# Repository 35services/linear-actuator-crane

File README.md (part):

# RC Crane – Stepper Linear Actuator Controller

**All CAD renderings and printable STLs:** [`cad/`](cad/README.md). **Carrier PCB, ready to order:**
[`pcb/`](pcb/README.md), as a through‑hole version for hand soldering or an SMD version
assembled by JLCPCB. **Advanced board** with an ESP32‑S3, 4 stepper drivers, 16 servo/ESC
outputs, RC and CRSF/SBUS inputs: [`pcb/advanced/`](pcb/advanced/README.md), or the same as a
[stack of two smaller boards](pcb/advanced-stack/README.md). The concept sketch
that started it is [`gemini.jpeg`](gemini.jpeg).

Drive two mini stepper‑motor linear actuators (2‑phase, 4‑wire, lead screw + slider) from
normal RC receiver channels to work a crane on an RC model vehicle:

* **Boom lift:** actuator 1 raises and lowers the boom.
* **Telescope:** actuator 2, lying on top of the boom, extends the inner boom section.

Features:

* **No end switches.** On power‑up both actuators home themselves using **sensorless
  homing** (TMC2209 StallGuard). If stall detection isn't reliable on your motors, they fall
  back to **hard‑stop homing**: each one drives into its mechanical end at low current.
* **Plug‑and‑play with RC.** The ESP32 reads a standard servo PWM signal (1000–2000 µs) from
  one receiver channel per actuator.
* **Battery friendly.** Lead screws are self‑locking, so the drivers are switched off when
  idle and the load still holds.

### Overview

| Crane, boom down | Crane, boom up 55°, telescope out |
|---|---|
|  |  |

**Bowden drives** ([use cases](cad/use-cases/README.md)): the actuator sits flat on the vehicle
and pushes or pulls a filament in a PTFE tube.

| Outriggers under the chassis | Crane with both actuators on the deck |
|---|---|
|  |  |

**Actuators** ([CAD](cad/README.md), [comparison](docs/actuator_comparison.md)):

| Stepper slider in a printed housing (used now) | 28BYJ‑48 + T8 lead screw (cheap stepper) | N20 + M4 lead screw (DC) |
|---|---|---|
|  |  |  |
| 75 mm stroke, 15–20 mm/s, exact position | 75 mm stroke, ≈ 2.7 mm/s, exact position, hall home sensor | 80 mm stroke, current‑sense homing |

**Boards** ([PCB overview](pcb/README.md)):

| Carrier, THT | Carrier, SMD (JLCPCB) | Advanced, ESP32‑S3 |
|---|---|---|
|  |  |  |
| ESP32‑C3, 2 × TMC2209, 80 × 64 mm | the same, SMD parts assembled | 4 × TMC2209, 16 PWM outputs, 100 × 100 mm |

| Advanced stack: top board | Advanced stack: bottom board | Web settings page |
|---|---|---|
|  |  |  |
| DevKitC‑1 + 4 drivers, 84 × 76 mm | PCA9685, inputs, power | [try it in the browser](https://raw.githack.com/35services/linear-actuator-crane/main/firmware/web_preview/index.html) |

---

## 1. How it works

```
                          ┌──── servo PWM (CH a) ──┐
 Transmitter ──radio──► RC receiver                ▼
                          └──── servo PWM (CH b) ──► ESP32-C3
                                                     │   ▲
                       shared UART + EN, own STEP/DIR│   │ DIAG (OR'ed)
                                     ┌───────────────┴───┴──────────────┐
                                     ▼                                  ▼
                              TMC2209 #0 (addr 0)               TMC2209 #1 (addr 1)
                                     │                                  │
                              actuator 1: boom lift             actuator 2: telescope
```

1. **Power‑up:** the ESP32 configures both TMC2209s over one shared UART line. They have
   different addresses, set with the MS1/MS2 pins.
2. **Homing,** one actuator at a time. The **telescope goes first**, so the boom moves with
   the shortest lever.
   * The actuator drives toward its retracted end at low current.
   * With **StallGuard**, the homing driver sees the motor load spike and pulls `DIAG`
     high, so the ESP32 stops right away. Only the homing driver has its stall output
     enabled, so the two `DIAG` lines can share one GPIO.
   * Without StallGuard (or if no stall is detected), the motor runs for the full stroke
     plus a small margin. At low current it just skips a few steps against the end, which
     does no harm, and that point becomes position 0.
   * Optionally, homing is skipped after a clean stop, see
     [Skipping homing after a clean stop](#skipping-homing-after-a-clean-stop).
3. **Run:** each RC channel controls one actuator, in either
   * **Position mode:** stick or knob position = actuator position. The default for the
     boom lift, best on a knob or slider.
   * **Rate mode:** stick deflection = speed. The default for the telescope, best on a
     self‑centring stick.
   Soft limits keep each slider a little away from both ends, so it never crashes again
   after homing.
4. **Failsafe:** if no valid RC pulse arrives on a channel for 250 ms, that actuator stops.

---

## 2. Components

| # | Qty | Part | Notes | ~Price |
|---|-----|------|-------|--------|
| 1 | **2** | Mini stepper linear actuator (the AliExpress part) | 2‑phase, 4‑wire. 18° (20 steps/rev), M3 screw with **0.5 mm lead**, **~75 mm stroke** (counted from the listing photo, see [Speed](#speed-how-fast-can-it-move)) | 2 × €11 |
| 2 | 1 | **ESP32‑C3 SuperMini** (or Seeed XIAO ESP32‑C3) | Tiny, 3.3 V logic, USB‑C | €3 |
| 3 | **2** | **TMC2209 stepper driver module** (BigTreeTech v1.3, FYSETC or similar, *UART version*) | Quiet (StealthChop), current set over UART, **StallGuard for sensorless homing**, 4.75–29 V | 2 × €4 |
| 4 | **2** | Electrolytic capacitor **100 µF, ≥ 25 V** (35 V recommended) | One across each driver's VM/GND, close to the module. **Required.** | €0.40 |
| 5 | 1 | Resistor **1 kΩ** | Single‑wire UART (between TX and the shared PDN_UART line) | – |
| 6 | 2 | Diode **1N4148** (or any small signal diode) | OR both `DIAG` outputs onto one GPIO | – |
| 7 | 1 | Resistor **10 kΩ** | Pull‑down on the shared `DIAG` line | – |
| 8 | 2 + 2 | Resistor **1 kΩ** + Schottky diode **BAT85** per RC channel | Series resistor + clamp to 3V3, so any receiver signal level (3.3 V, 5 V or the 7.4 V BEC rail) is safe | – |
| 9 | 1 | **LM2940CT‑5.0** low‑dropout regulator (TO‑220) | 5 V for the ESP32 from the 6 V / 7.4 V BEC rail. See [Power](#4-power) | €1.50 |
| 10 | 1 + 1 | Capacitors **470 nF** ceramic (LDO input) + **47 µF / 16 V** electrolytic (LDO output) | The LM2940 needs ≥ 22 µF on its output to be stable | – |
| 11 | 1 | Schottky diode **1N5817** | LDO → ESP32 5V pin. Stops USB from back‑feeding the regulator while flashing | – |
| 13 | 2 | Servo extension lead | Receiver channels → board | €2 |
| 15 | 1 set | Nesting square tubes (aluminium/brass, e.g. 16×12 and 11×7 mm) | Telescopic boom. See [Mechanics](#5-mechanics) | €5 |
| 16 | | [Carrier PCB](pcb/README.md) (or perfboard), JST‑XH connectors, female pin headers, heat‑shrink | | |

**Vehicle drive (for reference):** Hobbywing **QuicRun Fusion SE** 1800 kV crawler motor/ESC
combo. It takes 2–3S LiPo (up to 12.6 V) and has a switch‑mode **BEC of 6 V or 7.4 V
(switchable), 4 A**. The crane electronics are designed for both BEC settings.

### Why the TMC2209?

| Driver | Sensorless homing | Noise | Current setting | Verdict |
|--------|-------------------|-------|-----------------|---------|
| **TMC2209** | ✅ StallGuard4 | silent | software (UART) | **Recommended** |
| TMC2208 | ❌ | silent | potentiometer/UART | OK, hard‑stop homing only |
| A4988 / DRV8825 | ❌ | loud | potentiometer | Works, but crude for tiny motors |
| DRV8833 (H‑bridge) | ❌ | – | none (voltage‑driven) | Only for 5 V motors on a 5 V supply. No current limit |

> **What's the little potentiometer on the TMC2209 module for?** The onboard pot sets
> motor current in standalone mode via VREF, but since our firmware controls current over
> UART and disables VREF with `I_scale_analog(false)`, the pot has no effect and can be
> ignored.

---

## 3. Wiring diagram

Both drivers are wired the same way. The only differences are **STEP/DIR**, the **address
pins** and the **diode on DIAG**.

```
  2S/3S LiPo ──► Hobbywing QuicRun Fusion SE (ESC) ── BEC 6 V / 7.4 V, 4 A ──► RC receiver
                                                                                  │
         BEC + / − arrive on the board through the RC servo leads (CH a, CH b) ◄──┘
                     │
       ┌─────────────┤
       │ BEC + (VM)  │ GND (−)
       │      ┌──────┘
       │ (+)  │ (-)
       ├──────┼────────────────────────────────────────┐
       │      │      100 µF                    │      │      100 µF
       ▼      ▼     ┌─┤├─┐                     ▼      ▼     ┌─┤├─┐
   ┌───────────────────────────┐           ┌───────────────────────────┐
   │   TMC2209 #0 (boom lift)  │           │   TMC2209 #1 (telescope)  │
   │                           │           │                           │
   │  VM / GND ◄── BEC         │           │  VM / GND ◄── BEC         │
   │  1A 1B 2A 2B ──► actuator 1           │  1A 1B 2A 2B ──► actuator 2
   │                           │           │                           │
   │  VIO ◄── 3V3              │           │  VIO ◄── 3V3              │
   │  GND ◄── GND              │           │  GND ◄── GND              │
   │  MS1 ◄── GND  ┐ addr 0    │           │  MS1 ◄── 3V3  ┐ addr 1    │
   │  MS2 ◄── GND  ┘           │           │  MS2 ◄── GND  ┘           │
   │                           │           │                           │
   │  STEP ◄── GPIO4           │           │  STEP ◄── GPIO0           │
   │  DIR  ◄── GPIO5           │           │  DIR  ◄── GPIO1           │
   │  EN   ◄── GPIO6 (shared)  │           │  EN   ◄── GPIO6 (shared)  │
   │  DIAG ──►|──┐  1N4148     │           │  DIAG ──►|──┐  1N4148     │
   │             │             │           │             │             │
   │  PDN_UART ◄─┼──────┬──────────────────────── PDN_UART              │
   └─────────────┼──────┼──────┘           └─────────────┼─────────────┘
                 │      │                                │
                 │      │       DIAG (shared) ◄──────────┘
                 ├──────┼──────────────────────► GPIO7 ──[10 kΩ]── GND
                        │
                        ├──────────────────────► GPIO20 (RX)
                        └──[1 kΩ]──────────────► GPIO21 (TX)

                         470 nF        47 µF
                           ┴             ┴
   BEC + (6/7.4 V) ──► IN ┤ LM2940-5.0 ├ OUT ──►|── 1N5817 ──► SuperMini 5V
                              │ GND
                              ┴

   ┌────────────────────────┐                     ┌───────────────────────┐
   │     ESP32-C3 SuperMini │                     │      RC receiver      │
   │                        │                     │                       │
   │  5V  ◄── LM2940 (above)│          BEC + ◄──── + (6 V / 7.4 V)      │
   │  GND ◄──────────────────────────────────────── −                     │
   │  GPIO3  ◄──┬──[1 kΩ]──────────────────────────── S  CH a: boom lift   │
   │            └──►|── 3V3  (BAT85 clamp)         │                       │
   │  GPIO10 ◄──┬──[1 kΩ]──────────────────────────── S  CH b: telescope   │
   │            └──►|── 3V3  (BAT85 clamp)         └───────────────────────┘
   └────────────────────────┘
```

Each actuator connects to its driver exactly as before: one coil on `1A/1B`, the other on
`2A/2B`.

### Pin table

| ESP32‑C3 | → | Connects to | Purpose |
|----------|---|-------------|---------|
| GPIO4 | → | TMC2209 #0 STEP | boom lift step pulses |
| GPIO5 | → | TMC2209 #0 DIR | boom lift direction |
| GPIO0 | → | TMC2209 #1 STEP | telescope step pulses |
| GPIO1 | → | TMC2209 #1 DIR | telescope direction |
| GPIO6 | → | EN of **both** drivers | LOW = drivers on, HIGH = off |
| GPIO7 | ← | DIAG of **both**, through a diode each, plus 10 kΩ to GND | HIGH = stall detected |
| GPIO21 (TX) | → 1 kΩ → | PDN_UART of **both** | UART write |
| GPIO20 (RX) | ← | PDN_UART of **both** | UART read (direct) |
| GPIO3 | ← 1 kΩ ← | receiver CH a signal (BAT85 clamp to 3V3) | boom lift servo PWM in |
| GPIO10 | ← 1 kΩ ← | receiver CH b signal (BAT85 clamp to 3V3) | telescope servo PWM in |
| 3V3 | → | VIO of both, MS1 of #1 | logic supply / address |
| GND | – | GND of both drivers (logic side) | **common ground** |
| 5V | ← 1N5817 ← | LM2940‑5.0 output (input: BEC + from the receiver) | ESP32 supply |

### Wiring gotchas

* **Driver addresses:** #0 has MS1 = MS2 = GND (address 0). #1 has **MS1 = 3V3**,
  MS2 = GND (address 1). If both drivers have the same address, the UART check at boot
  fails for one of them.
* **DIAG – the stall signal for homing without end switches.** The TMC2209 pulls its DIAG
  pin high when the motor stalls (StallGuard).
  * **During homing:** the ESP32 watches GPIO7 and stops the actuator the moment it hits the
    end of travel.
  * **One GPIO for both drivers:** each DIAG goes through a diode (anode at DIAG, cathode
    (the band) toward GPIO7), and a 10 kΩ pull‑down holds the line low when neither driver
    signals a stall. The firmware only enables the stall output on the axis that is
    homing, so it always knows which one stalled.
  * **It needs a wire:** DIAG is **not** one of the 16 StepStick socket pins. On most
    modules it's a separate pin, and its position differs between brands. On the carrier
    PCB, run a short female‑to‑male Dupont jumper from the module's DIAG pin to the
    single socket next to the driver: **J12** for the lift, **J13** for the telescope.
  * **Without the wires:** set `USE_STALLGUARD false`, and homing drives into the end stop
    at low current instead.

* **Find the coil pairs** with a multimeter. The two wires that show resistance between them
  (typically 5–30 Ω) are one coil. If an actuator moves the wrong way, swap the two wires of
  **one** coil, or flip that axis's `invert` flag in the firmware.
* **Never plug or unplug a motor while its driver is powered.** That kills TMC drivers.
* Pin order differs between TMC2209 brands. Go by the labels, not by position.
  * BTT v1.3: `PDN_UART` is the pin marked **RX** (`TX` is the same net). `DIAG` is on the
    extra pin header at the top.
  * Some clones need a solder bridge to connect PDN to the header pin. Check the module's
    pinout.
* **All grounds are common:** ESC/BEC −, receiver −, ESP32 GND, both TMC2209 GNDs. With
  the carrier PCB this happens automatically through the servo leads.
* **Receiver signal level:** most receivers output 3.3 V signals, but some put out the
  servo rail voltage (up to 7.4 V with this BEC). The ESP32 isn't 5 V tolerant, so each
  channel has a 1 kΩ series resistor and a BAT85 Schottky diode from the GPIO to 3V3
  (cathode, the band, to 3V3). Anything above about 3.6 V is clamped, with at most about
  4 mA flowing into the 3V3 rail. This works with every receiver and needs no jumper.
* **Never connect the BEC + to the SuperMini's 5V pin directly.** At 6 V the onboard
  regulator is already at its limit, and 7.4 V destroys it. Always go through the LM2940.
* **Strapping pins:** GPIO2, 8 and 9 on the C3 are strapping pins and are avoided. GPIO0/1
  are normal GPIOs on the SuperMini.

---

## 4. Power

* **Everything runs from the ESC's BEC.** There's no separate battery input. The BEC
  arrives on the board through the `+`/`−` pins of the RC servo leads.
* **Motors (TMC2209 VM):** straight from the BEC rail (6 V or 7.4 V).
  * The TMC2209 works from 4.75 V, and the two small steppers draw only about 0.3–0.6 A
    together, against the 4 A BEC.
  * A "5 V" mini stepper is fine at 6–7.4 V. The TMC2209 limits the **current**, so the
    voltage only adds a little speed headroom.
  * Plug in **both** RC leads, so the current is shared between two servo cables.
  * A servo plug put on backwards is harmless: `+` is the middle pin, so only signal and
    GND swap. That's why there's no reverse‑polarity diode.
  * Set the current per axis in firmware (the `run` column in `AXES`). Rule of thumb:
    `I = rated voltage / coil resistance`. Example: 5 V / 15 Ω ≈ 330 mA → use about 300 mA.
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
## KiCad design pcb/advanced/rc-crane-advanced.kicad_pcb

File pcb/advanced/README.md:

# Advanced board – ESP32‑S3, 4 steppers, 16 PWM outputs

A 100 × 100 mm two‑layer board for the bigger concept: the ESP32 as receiver, as a
multiplexer between receiver and servos/ESC, or reading the drive channels in "crane mode".

| | |
|---|---|
| ESP32 | **ESP32‑S3‑DevKitC‑1** in two 1×22 sockets, USB over the left board edge |
| Steppers | **4 × TMC2209** StepStick sockets on one UART (addresses 0–3), DIAG per driver, 4 × JST‑XH motor connectors |
| Outputs | **16 servo/ESC outputs** from a PCA9685 (I²C), `S + −` block like a receiver, 220 Ω per channel |
| Inputs | **4 RC PWM inputs** (`S + −` block, 1 kΩ + clamp to 3V3) and a **CRSF/SBUS port** for a serial receiver |
| Extras | I²C header (second PCA9685, display, …) |
| Power | everything from the BEC rail; drivers' motor supply selectable: BEC or 2–3S battery |
| Assembly | 39 SMD parts by JLCPCB (12 part types, **1 extended**: the PCA9685), the rest hand‑soldered |
| DRC | 0 violations, 0 unconnected |

> **Smaller footprint?** The same circuit as a [stack of two 84 × 76 mm boards](../advanced-stack/README.md).

> **Status:** the board is designed and checked (DRC, netlist), but not built or tested yet.
> The current firmware is for the small ESP32‑C3 board; the firmware for this board
> (4 axes, PCA9685 outputs, CRSF/SBUS, crane mode) is the next step.

> **Which remote control?** RC/ELRS on the CRSF port, a PlayStation controller through a
> Bluepad32 bridge, or a WiFi app: see [remote control options](../../docs/remote_control_comparison.md).

| Top | Bottom |
|---|---|
|  |  |

| 3D, from below | Copper + silkscreen, front | Copper + silkscreen, back (mirrored) |
|---|---|---|
|  |  |  |

---

## ESP32 pin assignment

The DevKitC‑1 lies on its side: **USB connectors over the left board edge**, antenna to the
right over a copper‑free area. J10 is the board's J1 header (top row), J11 its J3 header.
Every socket pin is labelled on the silkscreen.

| GPIO | Function | | GPIO | Function |
|---|---|---|---|---|
| 4 / 5 | STEP / DIR driver #0 | | 1 | RC input 1 |
| 6 / 7 | STEP / DIR driver #1 | | 2 | RC input 2 |
| 15 / 16 | STEP / DIR driver #2 | | 42 | RC input 3 |
| 17 / 18 | STEP / DIR driver #3 | | 41 | RC input 4 |
| 8 | EN, all drivers (10 kΩ pull‑up: off at boot) | | 40 | serial receiver RX (CRSF/SBUS in) |
| 9 | TMC UART TX (via 1 kΩ) | | 39 | serial receiver TX (CRSF telemetry) |
| 10 | TMC UART RX (PDN_UART of all drivers) | | 47 / 21 | I²C SDA / SCL (PCA9685, I²C header) |
| 11 / 12 / 13 / 14 | DIAG driver #0 / #1 / #2 / #3 | | 48 | PCA9685 OE (10 kΩ pull‑up: outputs off at boot) |

**Kept free:** the strapping pins 0, 3, 45, 46; USB 19/20; 35–37 (used by the octal PSRAM
on N8R8/N16R8 modules); 38 (RGB LED on v1.1); 43/44 (USB‑UART, serial monitor).

* **DIAG inputs:** use the ESP's internal pull‑downs (`INPUT_PULLDOWN`).
* **SBUS** is an inverted signal. The S3's UART inverts it in hardware, no inverter
  needed.
* **v1.0 DevKitC‑1:** its RGB LED sits on GPIO48, which here is the PCA9685 OE line. That
  only makes the LED flicker.

## Connectors

| Ref | Connector | Pins |
|---|---|---|
| J4 | RC in, 3 × 4 block | rows `S + −`, channels 1–4 |
| J30 | PWM out, 3 × 16 block | rows `S + −`, channels 1–16 = PCA9685 LED0–15 |
| J7 | Serial receiver, 1 × 4 | `G 5V RX TX` (from the ESP's side: receiver TX → `RX`). Gets 5 V from the regulator: ELRS receivers want 5 V, not the 6–7.4 V BEC |
| J8 | I²C, 1 × 4 | `G 3V3 SDA SCL` |
| J9 | VM battery, screw terminal | `+ −`, 2–3S LiPo, through an SS34 diode (reverse polarity) |
| J20–J23 | Motors, JST‑XH 4 | `1A 1B 2A 2B` |
| J12–J15 | DIAG, 1 × 1 socket | jumper wire from each module's DIAG pin, see [main README](../../README.md#3-wiring-diagram) |

## Power

* **One rail like in a receiver:** the `+` pins of all 20 three‑pin headers (RC in and
  PWM out) are one rail, VBEC. The ESC plugged into an output powers the whole board
  through its BEC, and every servo gets its power from the same rail. C7 (1000 µF) buffers
  servo current peaks.
* **ESP32 and serial receiver:** 5 V from an AMS1117‑5.0 on VBEC, then a Schottky diode to
  the DevKit's 5V pin, so USB can't back‑feed the regulator.
* **Driver motor supply (VM): bridge JP9, the drivers get no motor power until you do.**
  * `BEC` side (pads 2–3): from the BEC rail, like the small boards.
  * `BATT` side (pads 1–2): from a 2–3S battery on J9. That takes the stepper load off the
    4 A BEC when many servos run too. The TMC2209 is fine with up to 29 V.
  * Never bridge all three pads.
* Up to 16 servos can draw far more than 4 A. For many or strong servos use a stronger
  external BEC on the rail, and then **remove the red wire of the ESC's lead**, so two BECs
  never fight.

## Ordering (JLCPCB)

| File | Upload as |
|------|-----------|
| [`fab/rc-crane-advanced-gerbers.zip`](fab/rc-crane-advanced-gerbers.zip) | Gerber file |
| [`jlcpcb_bom.csv`](jlcpcb_bom.csv) | BOM |
| [`jlcpcb_cpl.csv`](jlcpcb_cpl.csv) | CPL / pick‑and‑place |

Settings as for the [SMD carrier](../smd/README.md#ordering-steps): 2 layers, 1.6 mm,
assembly on the top side, "Confirm Parts Placement" on. In the placement preview, check:

| Ref | Polarity mark |
|---|---|
| U5 (PCA9685) | pin 1 dot, top left |
| U4 (AMS1117) | tab = OUT, the three pins on the left |
| D4, D20–D23 (B5819W), D9 (SS34) | cathode band = pad 1 |

**Extended parts:** only the PCA9685 ([C2678753](https://www.lcsc.com/product-detail/C2678753.html),
fallback C92206), so one setup fee of about $3. Everything else is a basic part. See
[extended parts](../README.md#jlcpcb-extended-parts-cost-tracking) and
`python3 pcb/check_jlc_parts.py` for current stock.

### Hand‑soldered

| Ref | Part |
|---|---|
| J10, J11 | 2 × female header 1×22, 2.54 mm – DevKitC‑1 |
| U10–U13 | 8 × female header 1×8 – TMC2209 sockets |
| J12–J15 | 4 × female header 1×1 – DIAG |
| J20–J23 | 4 × JST‑XH 4‑pin B4B‑XH‑A – motors |
| J4 | pin headers for a 3 × 4 block (e.g. 3 × 1×4 or cut from a 3×40 strip) |
| J30 | pin headers for a 3 × 16 block |
| J7, J8 | pin header 1×4 |
| J9 | screw terminal 2‑pin, 5.08 mm (only if you use the battery input) |
| C1–C4 | 100 µF 25 V electrolytic, D5 mm, 2 mm pitch – driver VM buffer, **required** |
| C7 | 1000 µF 16 V electrolytic, D10 mm, 5 mm pitch – servo rail buffer |
| JP1–JP4 | UART pin 4/5 per driver brand, see the [PCB README](../README.md#before-you-order-check-these-both-variants) |
| JP9 | VM source, see [Power](#power) |

## Before you order

1. **DevKitC‑1 clone pinout.** The board follows Espressif's v1.1 drawing (25.4 × 62.74 mm,
   rows 22.86 mm apart, pin 1 = 3V3 / G at the antenna end). Lay your board on the top
   render and compare the pin labels.
2. **TMC2209 modules and UART pin:** as for the small boards, see the
   [PCB README](../README.md#before-you-order-check-these-both-variants). Addresses are
   fixed by copper: #0 = 0, #1 = 1 (MS1 high), #2 = 2 (MS2 high), #3 = 3 (both high).

## Rebuilding

```bash
./pcb/build.sh advanced          # place, route, clean up, pour, DRC, Gerbers, renders
./pcb/build.sh advanced outputs  # only DRC + Gerbers + renders from the existing board
```

Everything is in [`generate_advanced.py`](generate_advanced.py): the pin map (`ESP_NETS`),
the parts table and the silkscreen. After autorouting it removes vias that only connect one layer, widens the
router's neck‑downs to 0.15 mm where the clearance allows, and adds GND stitching vias so
both ground pours are one net. That code is shared with the stacked boards in
[`../board_tools.py`](../board_tools.py).

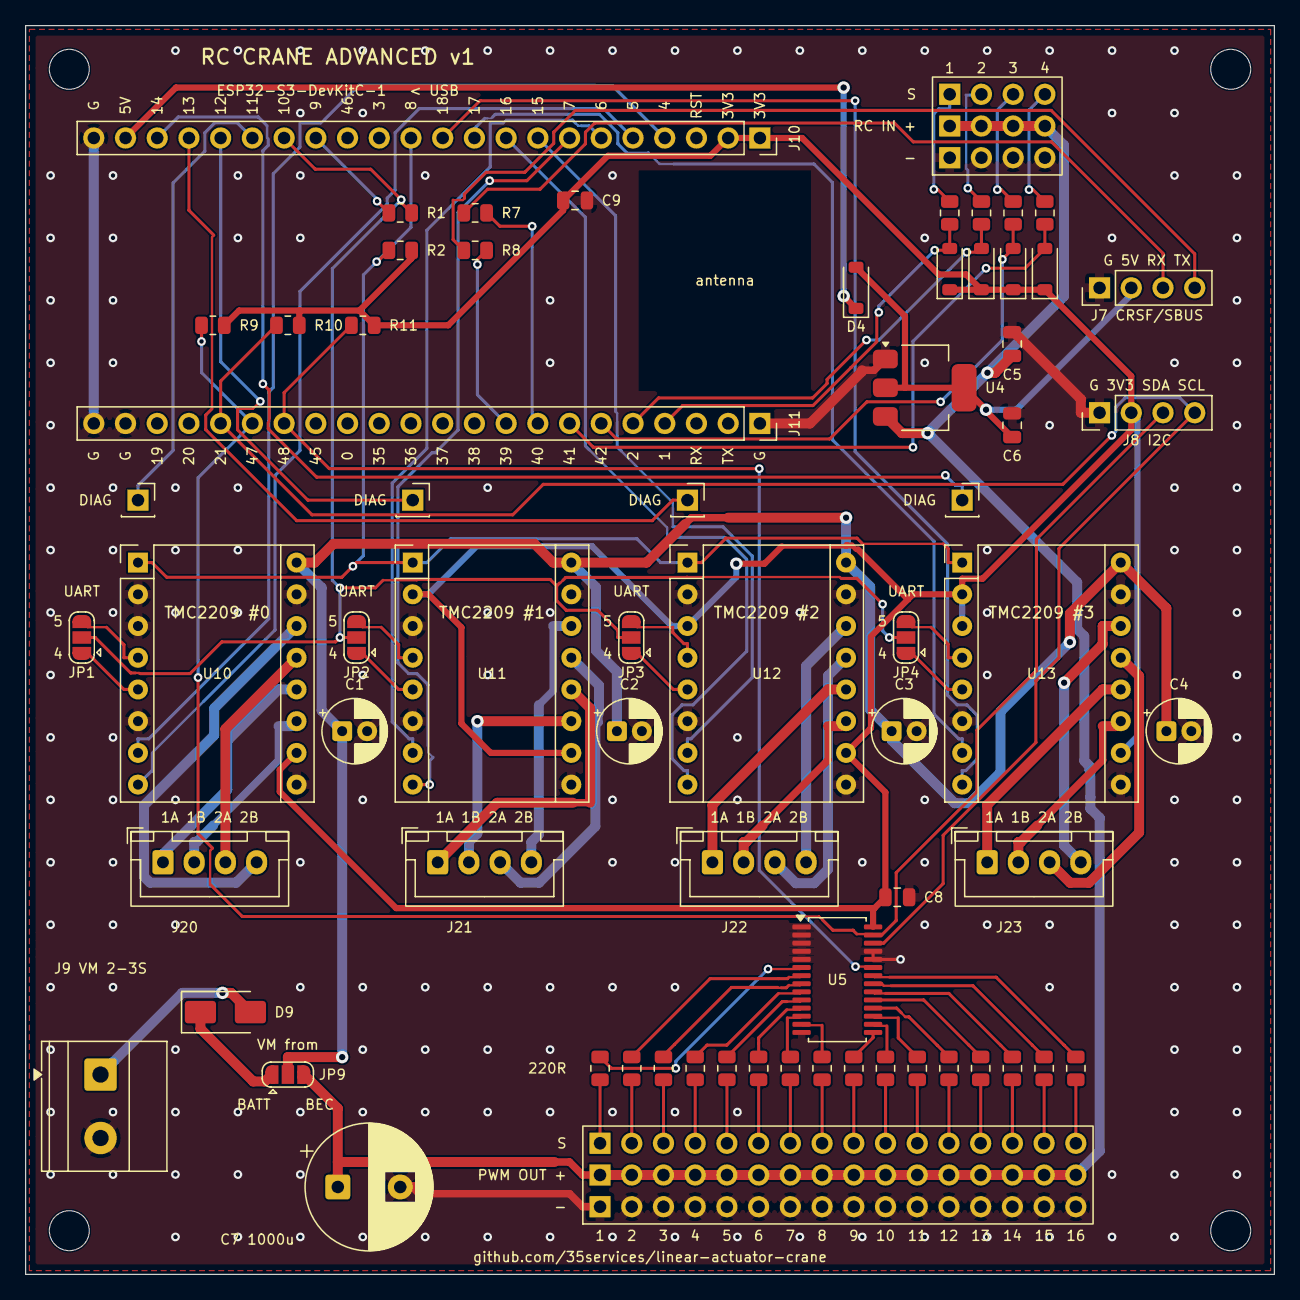
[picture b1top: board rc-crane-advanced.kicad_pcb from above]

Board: 2 copper layers, 100.0 x 100.0 mm, 72 parts (0 on the bottom side), 94 nets.

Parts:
C1, C2, C3, C4: 100u 25V; CP_Radial_D5.0mm_P2.00mm
C5, C9: 10u 25V; C_0805_2012Metric
C6: 22u 25V; C_0805_2012Metric
C7: 1000u 16V; CP_Radial_D10.0mm_P5.00mm
C8: 100n; C_0805_2012Metric
D4, D20, D21, D22, D23: B5819W; D_SOD-123
D9: SS34; D_SMA
H1, H2, H3, H4: MountingHole_3.2mm_M3
J4: RC in; PinHeader_3x04_P2.54mm
J7: Serial RX; PinHeader_1x04_P2.54mm_Vertical
J8: I2C; PinHeader_1x04_P2.54mm_Vertical
J9: VM batt; TerminalBlock_Phoenix_MKDS-1,5-2-5.08_1x02_P5.08mm_Horizont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
J10: DevKitC-1 J1; PinSocket_1x22_P2.54mm_Vertical
J11: DevKitC-1 J3; PinSocket_1x22_P2.54mm_Vertical
J12: DIAG0; PinSocket_1x01_P2.54mm_Vertical
J13: DIAG1; PinSocket_1x01_P2.54mm_Vertical
J14: DIAG2; PinSocket_1x01_P2.54mm_Vertical
J15: DIAG3; PinSocket_1x01_P2.54mm_Vertical
J20: Motor 0; JST_XH_B4B-XH-A_1x04_P2.50mm_Vertical
J21: Motor 1; JST_XH_B4B-XH-A_1x04_P2.50mm_Vertical
J22: Motor 2; JST_XH_B4B-XH-A_1x04_P2.50mm_Vertical
J23: Motor 3; JST_XH_B4B-XH-A_1x04_P2.50mm_Vertical
J30: PWM out; PinHeader_3x16_P2.54mm
JP1, JP2, JP3, JP4: UART 4|5; SolderJumper-3_P1.3mm_Open_RoundedPad1.0x1.5mm
JP9: VM BEC|BATT; SolderJumper-3_P1.3mm_Open_RoundedPad1.0x1.5mm
R1, R7, R8, R20, R21, R22, R23: 1k; R_0805_2012Metric
R2, R11: 10k; R_0805_2012Metric
R9, R10: 4.7k; R_0805_2012Metric
R40, R41, R42, R43, R44, R45, R46, R47, R48, R49, R50, R51, R52, R53, R54, R55: 220; R_0805_2012Metric
U4: AMS1117-5.0; SOT-223-3_TabPin2
U5: PCA9685PW; TSSOP-28_4.4x9.7mm_P0.65mm
U10: TMC2209 #0; Pololu_Breakout-16_15.2x20.3mm
U11: TMC2209 #1; Pololu_Breakout-16_15.2x20.3mm
U12: TMC2209 #2; Pololu_Breakout-16_15.2x20.3mm
U13: TMC2209 #3; Pololu_Breakout-16_15.2x20.3mm

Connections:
+3V3: C8.1, C9.1, D20.1, D21.1, D22.1, D23.1, J8.2, J10.1, J10.2, R2.2, R9.2, R10.2, R11.2, U5.28, U10.10, U11.2, U11.10, U12.3, U12.10, U13.2, U13.3, U13.10
+5V: D4.1, J10.21
+5V_REG: C6.1, D4.2, J7.2, U4.2
DIAG0: J10.17, J12.1
DIAG1: J10.18, J13.1
DIAG2: J10.19, J14.1
DIAG3: J10.20, J15.1
DIR0: J10.5, U10.8
DIR1: J10.7, U11.8
DIR2: J10.9, U12.8
DIR3: J10.11, U13.8
EN: J10.12, R2.1, U10.1, U11.1, U12.1, U13.1
GND: C1.2, C2.2, C3.2, C4.2, C5.2, C6.2, C7.2, C8.2, C9.2, J4.9, J4.10, J4.11, J4.12, J7.1, J8.1, J9.2, J10.22, J11.1, J11.21, J11.22, J30.33, J30.34, J30.35, J30.36, J30.37, J30.38, J30.39, J30.40, J30.41, J30.42, J30.43, J30.44, J30.45, J30.46, J30.47, J30.48, U4.1, U5.1, U5.2, U5.3, U5.4, U5.5, U5.14, U5.24, U5.25, U10.2, U10.3, U10.6, U10.9, U10.15, U11.3, U11.6, U11.9, U11.15, U12.2, U12.6, U12.9, U12.15, U13.6, U13.9, U13.15
LED0: R40.2, U5.6
LED1: R41.2, U5.7
LED2: R42.2, U5.8
LED3: R43.2, U5.9
LED4: R44.2, U5.10
LED5: R45.2, U5.11
LED6: R46.2, U5.12
LED7: R47.2, U5.13
LED8: R48.2, U5.15
LED9: R49.2, U5.16
LED10: R50.2, U5.17
LED11: R51.2, U5.18
LED12: R52.2, U5.19
LED13: R53.2, U5.20
LED14: R54.2, U5.21
LED15: R55.2, U5.22
M0_1A: J20.1, U10.12
M0_1B: J20.2, U10.11
M0_2A: J20.3, U10.13
M0_2B: J20.4, U10.14
M1_1A: J21.1, U11.12
M1_1B: J21.2, U11.11
M1_2A: J21.3, U11.13
M1_2B: J21.4, U11.14
M2_1A: J22.1, U12.12
M2_1B: J22.2, U12.11
M2_2A: J22.3, U12.13
M2_2B: J22.4, U12.14
M3_1A: J23.1, U13.12
M3_1B: J23.2, U13.11
M3_2A: J23.3, U13.13
M3_2B: J23.4, U13.14
PWM0: J30.1, R40.1
PWM1: J30.2, R41.1
PWM2: J30.3, R42.1
PWM3: J30.4, R43.1
PWM4: J30.5, R44.1
PWM5: J30.6, R45.1
PWM6: J30.7, R46.1
PWM7: J30.8, R47.1
PWM8: J30.9, R48.1
PWM9: J30.10, R49.1
PWM10: J30.11, R50.1
PWM11: J30.12, R51.1
PWM12: J30.13, R52.1
PWM13: J30.14, R53.1
PWM14: J30.15, R54.1
PWM15: J30.16, R55.1
PWM_OE: J11.16, R11.1, U5.23
RC0: D20.2, J11.4, R20.1
RC0_IN: J4.1, R20.2
RC1: D21.2, J11.5, R21.1
RC1_IN: J4.2, R21.2
RC2: D22.2, J11.6, R22.1
RC2_IN: J4.3, R22.2
RC3: D23.2, J11.7, R23.1
RC3_IN: J4.4, R23.2
SCL: J8.4, J11.18, R10.1, U5.26
SDA: J8.3, J11.17, R9.1, U5.27
SRX: J11.8, R7.2
SRX_IN: J7.3, R7.1
STEP0: J10.4, U10.7
STEP1: J10.6, U11.7
STEP2: J10.8, U12.7
STEP3: J10.10, U13.7
STX: J11.9, R8.2
STX_OUT: J7.4, R8.1
U0_P4: JP1.3, U10.4
U0_P5: JP1.1, U10.5
U1_P4: JP2.3, U11.4
U1_P5: JP2.1, U11.5
U2_P4: JP3.3, U12.4
U2_P5: JP3.1, U12.5
U3_P4: JP4.3, U13.4
U3_P5: JP4.1, U13.5
UART: J10.16, JP1.2, JP2.2, JP3.2, JP4.2, R1.2
UART_TX: J10.15, R1.1
VBAT: D9.1, JP9.1
VBAT_IN: D9.2, J9.1
VBEC: C5.1, C7.1, J4.5, J4.6, J4.7, J4.8, J30.17, J30.18, J30.19, J30.20, J30.21, J30.22, J30.23, J30.24, J30.25, J30.26, J30.27, J30.28, J30.29, J30.30, J30.31, J30.32, JP9.3, U4.3
VM: C1.1, C2.1, C3.1, C4.1, JP9.2, U10.16, U11.16, U12.16, U13.16

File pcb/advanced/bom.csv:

Qty,References,Value,Footprint,LCSC
4,"C1 C2 C3 C4","100u 25V","Capacitor_THT:CP_Radial_D5.0mm_P2.00mm",""
2,"C5 C9","10u 25V","Capacitor_SMD:C_0805_2012Metric","C15850"
1,"C6","22u 25V","Capacitor_SMD:C_0805_2012Metric","C45783"
1,"C7","1000u 16V","Capacitor_THT:CP_Radial_D10.0mm_P5.00mm",""
1,"C8","100n","Capacitor_SMD:C_0805_2012Metric","C49678"
5,"D4 D20 D21 D22 D23","B5819W","Diode_SMD:D_SOD-123","C8598"
1,"D9","SS34","Diode_SMD:D_SMA","C8678"
1,"J10","DevKitC-1 J1","Connector_PinSocket_2.54mm:PinSocket_1x22_P2.54mm_Vertical",""
1,"J11","DevKitC-1 J3","Connector_PinSocket_2.54mm:PinSocket_1x22_P2.54mm_Vertical",""
1,"J12","DIAG0","Connector_PinSocket_2.54mm:PinSocket_1x01_P2.54mm_Vertical",""
1,"J13","DIAG1","Connector_PinSocket_2.54mm:PinSocket_1x01_P2.54mm_Vertical",""
1,"J14","DIAG2","Connector_PinSocket_2.54mm:PinSocket_1x01_P2.54mm_Vertical",""
1,"J15","DIAG3","Connector_PinSocket_2.54mm:PinSocket_1x01_P2.54mm_Vertical",""
1,"J20","Motor 0","Connector_JST:JST_XH_B4B-XH-A_1x04_P2.50mm_Vertical",""
1,"J21","Motor 1","Connector_JST:JST_XH_B4B-XH-A_1x04_P2.50mm_Vertical",""
1,"J22","Motor 2","Connector_JST:JST_XH_B4B-XH-A_1x04_P2.50mm_Vertical",""
1,"J23","Motor 3","Connector_JST:JST_XH_B4B-XH-A_1x04_P2.50mm_Vertical",""
1,"J30","PWM out","rc_crane:PinHeader_3x16_P2.54mm",""
1,"J4","RC in","rc_crane:PinHeader_3x04_P2.54mm",""
1,"J7","Serial RX","Connector_PinHeader_2.54mm:PinHeader_1x04_P2.54mm_Vertical",""
1,"J8","I2C","Connector_PinHeader_2.54mm:PinHeader_1x04_P2.54mm_Vertical",""
1,"J9","VM batt","TerminalBlock_Phoenix:TerminalBlock_Phoenix_MKDS-1,5-2-5.08_1x02_P5.08mm_Horizontal",""
4,"JP1 JP2 JP3 JP4","UART 4|5","Jumper:SolderJumper-3_P1.3mm_Open_RoundedPad1.0x1.5mm",""
1,"JP9","VM BEC|BATT","Jumper:SolderJumper-3_P1.3mm_Open_RoundedPad1.0x1.5mm",""
7,"R1 R7 R8 R20 R21 R22 R23","1k","Resistor_SMD:R_0805_2012Metric","C17513"
2,"R2 R11","10k","Resistor_SMD:R_0805_2012Metric","C17414"
16,"R40 R41 R42 R43 R44 R45 R46 R47 R48 R49 R50 R51 R52 R53 R54 R55","220","Resistor_SMD:R_0805_2012Metric","C17557"
2,"R9 R10","4.7k","Resistor_SMD:R_0805_2012Metric","C17673"
1,"U10","TMC2209 #0","Module:Pololu_Breakout-16_15.2x20.3mm",""
1,"U11","TMC2209 #1","Module:Pololu_Breakout-16_15.2x20.3mm",""
1,"U12","TMC2209 #2","Module:Pololu_Breakout-16_15.2x20.3mm",""
1,"U13","TMC2209 #3","Module:Pololu_Breakout-16_15.2x20.3mm",""
1,"U4","AMS1117-5.0","Package_TO_SOT_SMD:SOT-223-3_TabPin2","C6187"
1,"U5","PCA9685PW","Package_SO:TSSOP-28_4.4x9.7mm_P0.65mm","C2678753"

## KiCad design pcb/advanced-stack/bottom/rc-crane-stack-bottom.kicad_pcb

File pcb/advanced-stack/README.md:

# Advanced board, stacked – two 84 × 76 mm boards

The [advanced board](../advanced/README.md) split in two and stacked: about **half the
footprint** of the single 100 × 100 mm board, at the cost of height and a second PCB. Same
circuit, same ESP32 pin assignment, so the same firmware runs on both versions.

| Top board – drivers | Bottom board – I/O |
|---|---|
|  |  |
| ESP32‑S3‑DevKitC‑1, 4 × TMC2209, 4 motor connectors, DIAG sockets, UART jumpers | PCA9685 + 16 servo/ESC outputs, 4 RC inputs, CRSF/SBUS, I²C, 5 V regulator, motor supply input |
| **Through‑hole only**, no assembly needed | **SMD assembled by JLCPCB** (37 placements, PCA9685 is the only extended part) |
| DRC: 0 violations, 0 unconnected | DRC: 0 violations, 0 unconnected |

> **Status:** designed and checked (DRC, same netlist as the single board), not built yet.

## How the stack goes together

```
         DevKitC-1                 TMC2209 modules
     ┌───────────────┐         ┌──┐ ┌──┐
     │  in sockets   │         │  │ │  │
  ═══╧═══════════════╧═════════╧══╧═╧══╧═══   top board (drivers)
   ║      ▼ J1 male header, soldered in from below          ║  M3 standoffs
   ║  ┌────────┐                                            ║  ~11 mm
   ║  │ J1 2x8 │    PCA9685   ...                           ║
  ═╪══╧════════╧═══════════════════════════════════════════╪═  bottom board (I/O)
 ◄═╡ RC in, CRSF, I2C                   PWM out 1-16  ═══►  ═╡ VM in
   right-angle headers, pointing out of the board edges        C7 (1000 µF) underneath
```

* **Connection:** a 2×8 stacking pair, **J1**. The bottom board gets a female header
  (8.5 mm), the top board a male header soldered in **from the bottom side**. Same
  position on both boards. That gives about 11 mm between the boards.
* **Mechanics:** 4 M3 holes at the same positions on both boards. Use 11 mm spacers between
  the boards (female/female) and standoffs below the bottom board.
* **Everything on the bottom board is reachable from the side:** the RC inputs, CRSF and I²C
  headers point out of the left edge, the 16 outputs out of the bottom edge, the motor
  supply (side‑entry JST‑XH) out of the right edge. All are lower than the 11 mm gap.
* **C7 (1000 µF servo buffer) sits on the underside** of the bottom board, so it doesn't
  need room in the gap. Leave about 17 mm under the stack, or lay it flat.

### J1 – what goes between the boards

| Pin | Net | | Pin | Net |
|---|---|---|---|---|
| 1 | GND | | 2 | GND |
| 3 | VM (motor supply, from JP9) | | 4 | VM |
| 5 | +5V (to the DevKit) | | 6 | +3V3 (from the DevKit) |
| 7 | RC input 1 → GPIO1 | | 8 | RC input 2 → GPIO2 |
| 9 | RC input 3 → GPIO42 | | 10 | RC input 4 → GPIO41 |
| 11 | serial RX → GPIO40 | | 12 | serial TX ← GPIO39 |
| 13 | SDA (GPIO47) | | 14 | SCL (GPIO21) |
| 15 | PCA9685 OE (GPIO48) | | 16 | GND |

VM uses two pins (about 3 A each), more than the four small steppers need.

---

## Top board – drivers

* **DevKitC‑1 standing on its head:** USB at the top board edge, antenna at the bottom over
  a copper‑free area. The STEP/DIR/UART/DIAG row faces the drivers.
* **4 TMC2209 in a 2 × 2 grid**, each with DIAG socket, UART pin jumper (JP1–JP4, same as
  the small boards), JST‑XH motor connector and 100 µF VM capacitor. Addresses 0–3 are set by
  copper.
* R1 (1 kΩ UART) and R2 (10 kΩ EN pull‑up) are through‑hole, under the DevKit.

| Ref | Part |
|---|---|
| J10, J11 | 2 × female header 1×22 – DevKitC‑1 |
| U10–U13 | 8 × female header 1×8 – TMC2209 sockets |
| J12–J15 | 4 × female header 1×1 – DIAG |
| J20–J23 | 4 × JST‑XH 4‑pin B4B‑XH‑A – motors |
| C1–C4 | 100 µF 25 V electrolytic, D5 mm, 2 mm pitch |
| R1, R2 | 1 kΩ, 10 kΩ, axial |
| J1 | male header 2×8, 2.54 mm – **solder it in from the bottom side** |
| JP1–JP4 | solder jumpers, UART pin 4/5 |

## Bottom board – I/O

| Ref | Connector | Pins |
|---|---|---|
| J4 | RC in, right angle 3 × 4, left edge | rows from the board: `−` `+` `S`, channel 1 at the top |
| J7 | Serial receiver, right angle 1 × 4, left edge | `G 5V RX TX` (5 V for ELRS receivers) |
| J8 | I²C, right angle 1 × 4, left edge | `G 3V3 SDA SCL` |
| J30 | PWM out, right angle 3 × 16, bottom edge | rows from the board: `−` `+` `S`, channel 1 on the left |
| J9 | Motor supply, JST‑XH 2‑pin side entry, right edge | `+ −`, 2–3S, through an SS34 |
| J1 | to the top board, female 2×8 | see above |

* **JP9 selects the motor supply, as on the single board:** bridge `BEC` (pads 2–3) or
  `BATT` (pads 1–2). The drivers get no motor power until you do.
* The servo rows on the side headers are stacked on top of each other: `−` lowest (next to
  the board), `S` on top. Plug the servo leads in with the signal wire up.

| Hand‑soldered | |
|---|---|
| J4 | right‑angle pin headers for a 3 × 4 block (3‑row right‑angle header, cut to length) |
| J30 | right‑angle 3‑row header, 16 columns |
| J7, J8 | right‑angle pin header 1×4 |
| J9 | JST‑XH S2B‑XH‑A (side entry) |
| J1 | female header 2×8, 8.5 mm |
| C7 | 1000 µF 16 V electrolytic, D10 mm, **on the bottom side** |
| JP9 | solder jumper, VM source |

**Ordering:** upload `bottom/fab/rc-crane-stack-bottom-gerbers.zip`, `bottom/jlcpcb_bom.csv`
and `bottom/jlcpcb_cpl.csv` as described for the
[advanced board](../advanced/README.md#ordering-jlcpcb), with the same polarity checks. The
top board is a plain PCB order: `top/fab/rc-crane-stack-top-gerbers.zip`.

## Single board or stack?

| | [Single](../advanced/README.md) | Stack |
|---|---|---|
| Footprint | 100 × 100 mm | **84 × 76 mm** |
| Height (without DevKit/modules) | one board | two boards, ~11 mm apart |
| PCBs / assembly orders | 1 / 1 | 2 / 1 (the top board needs no assembly) |
| Servo/RC connectors | vertical, plug from above | right angle, plug from the side |
| Cost | lowest | a second PCB, a few euros more |

## Rebuilding

```bash
./pcb/build.sh stack          # both boards
./pcb/build.sh stack-top      # one board
```

[`generate_stack.py`](generate_stack.py) holds both boards' tables and shares the outline,
holes and J1 position between them. The board building itself is
[`../board_tools.py`](../board_tools.py), the same as for the single advanced board.

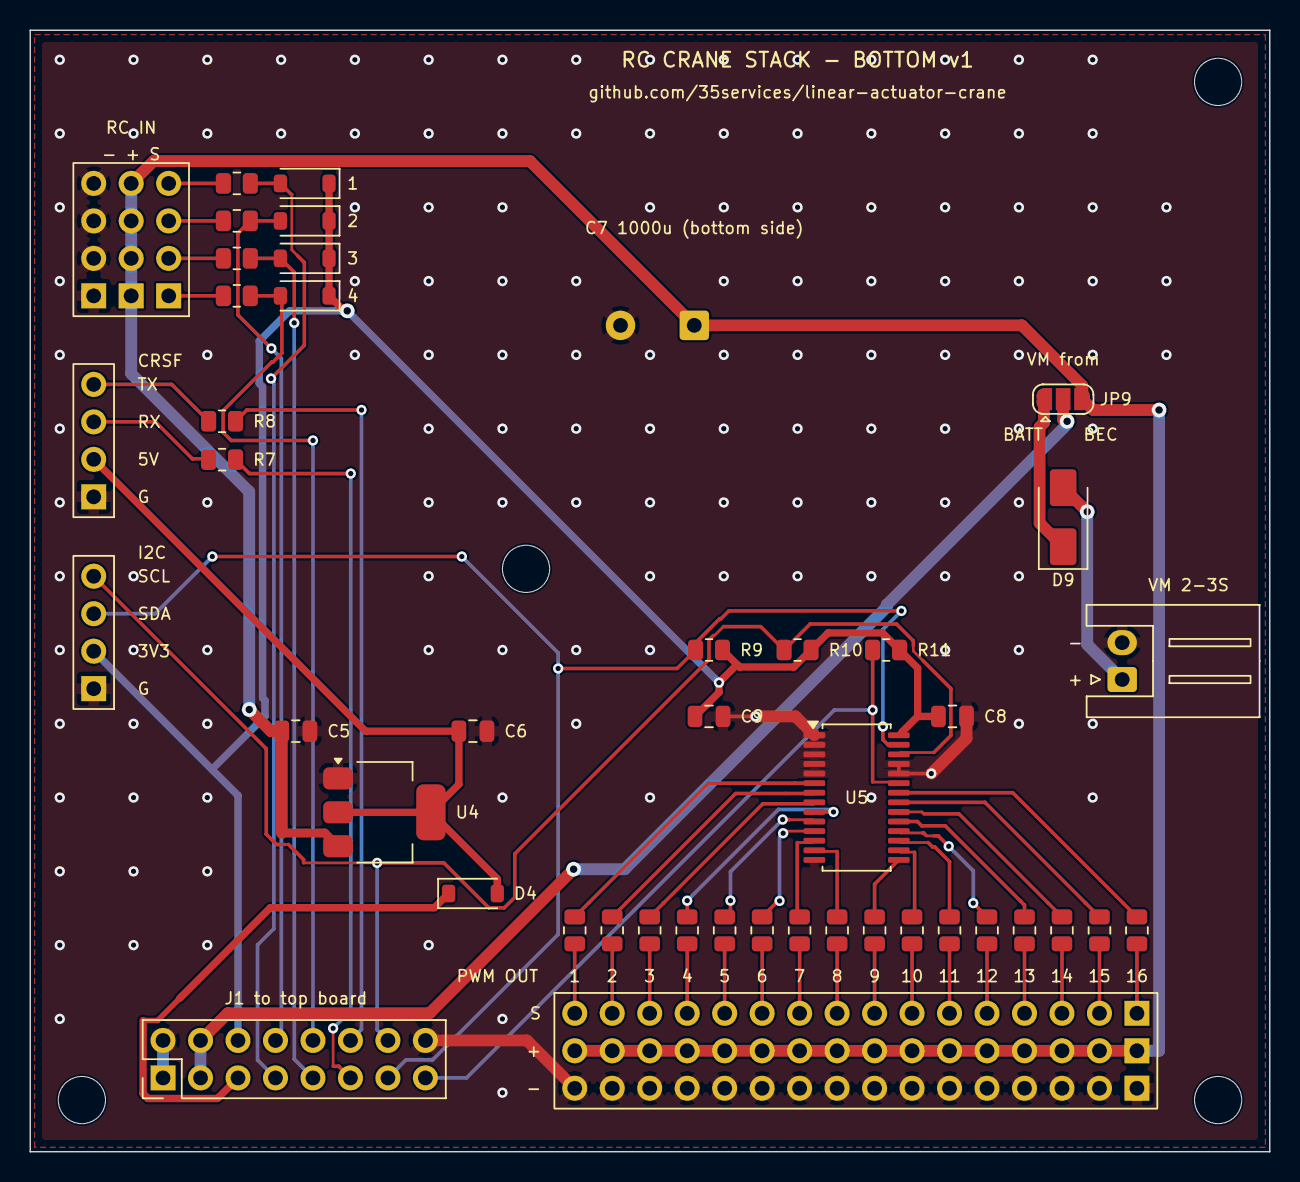
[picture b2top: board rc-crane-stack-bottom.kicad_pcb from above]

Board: 2 copper layers, 84.0 x 76.0 mm, 49 parts (1 on the bottom side), 55 nets.

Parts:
C5, C9: 10u 25V; C_0805_2012Metric
C6: 22u 25V; C_0805_2012Metric
C7: 1000u 16V; CP_Radial_D10.0mm_P5.00mm
C8: 100n; C_0805_2012Metric
D4, D20, D21, D22, D23: B5819W; D_SOD-123
D9: SS34; D_SMA
H1, H2, H3, H4: MountingHole_3.2mm_M3
J1: 2x8 female 8.5 mm; PinHeader_2x08_P2.54mm_Vertical
J4: RC in, right angle; PinHeader_3x04_P2.54mm_Horizontal
J7: Serial RX, right angle; PinHeader_1x04_P2.54mm_Horizontal
J8: I2C, right angle; PinHeader_1x04_P2.54mm_Horizontal
J9: VM batt, side entry; JST_XH_S2B-XH-A_1x02_P2.50mm_Horizontal
J30: PWM out, right angle; PinHeader_3x16_P2.54mm_Horizontal
JP9: VM BEC|BATT; SolderJumper-3_P1.3mm_Open_RoundedPad1.0x1.5mm
R7, R8, R20, R21, R22, R23: 1k; R_0805_2012Metric
R9, R10: 4.7k; R_0805_2012Metric
R11: 10k; R_0805_2012Metric
R40, R41, R42, R43, R44, R45, R46, R47, R48, R49, R50, R51, R52, R53, R54, R55: 220; R_0805_2012Metric
U4: AMS1117-5.0; SOT-223-3_TabPin2
U5: PCA9685PW; TSSOP-28_4.4x9.7mm_P0.65mm

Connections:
+3V3: C8.1, C9.1, D20.1, D21.1, D22.1, D23.1, J1.6, J8.2, R9.2, R10.2, R11.2, U5.28
+5V: D4.1, J1.5
+5V_REG: C6.1, D4.2, J7.2, U4.2
GND: C5.2, C6.2, C7.2, C8.2, C9.2, J1.1, J1.2, J1.16, J4.1, J4.2, J4.3, J4.4, J7.1, J8.1, J9.2, J30.1, J30.2, J30.3, J30.4, J30.5, J30.6, J30.7, J30.8, J30.9, J30.10, J30.11, J30.12, J30.13, J30.14, J30.15, J30.16, U4.1, U5.1, U5.2, U5.3, U5.4, U5.5, U5.14, U5.24, U5.25
LED0: R40.2, U5.6
LED1: R41.2, U5.7
LED2: R42.2, U5.8
LED3: R43.2, U5.9
LED4: R44.2, U5.10
LED5: R45.2, U5.11
LED6: R46.2, U5.12
LED7: R47.2, U5.13
LED8: R48.2, U5.15
LED9: R49.2, U5.16
LED10: R50.2, U5.17
LED11: R51.2, U5.18
LED12: R52.2, U5.19
LED13: R53.2, U5.20
LED14: R54.2, U5.21
LED15: R55.2, U5.22
PWM0: J30.48, R40.1
PWM1: J30.47, R41.1
PWM2: J30.46, R42.1
PWM3: J30.45, R43.1
PWM4: J30.44, R44.1
PWM5: J30.43, R45.1
PWM6: J30.42, R46.1
PWM7: J30.41, R47.1
PWM8: J30.40, R48.1
PWM9: J30.39, R49.1
PWM10: J30.38, R50.1
PWM11: J30.37, R51.1
PWM12: J30.36, R52.1
PWM13: J30.35, R53.1
PWM14: J30.34, R54.1
PWM15: J30.33, R55.1
PWM_OE: J1.15, R11.1, U5.23
RC0: D20.2, J1.7, R20.2
RC0_IN: J4.12, R20.1
RC1: D21.2, J1.8, R21.2
RC1_IN: J4.11, R21.1
RC2: D22.2, J1.9, R22.2
RC2_IN: J4.10, R22.1
RC3: D23.2, J1.10, R23.2
RC3_IN: J4.9, R23.1
SCL: J1.14, J8.4, R10.1, U5.26
SDA: J1.13, J8.3, R9.1, U5.27
SRX: J1.11, R7.2
SRX_IN: J7.3, R7.1
STX: J1.12, R8.2
STX_OUT: J7.4, R8.1
VBAT: D9.1, JP9.1
VBAT_IN: D9.2, J9.1
VBEC: C5.1, C7.1, J4.5, J4.6, J4.7, J4.8, J30.17, J30.18, J30.19, J30.20, J30.21, J30.22, J30.23, J30.24, J30.25, J30.26, J30.27, J30.28, J30.29, J30.30, J30.31, J30.32, JP9.3, U4.3
VM: J1.3, J1.4, JP9.2

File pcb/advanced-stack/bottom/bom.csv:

Qty,References,Value,Footprint,LCSC
1,"C6","22u 25V","Capacitor_SMD:C_0805_2012Metric","C45783"
1,"C7","1000u 16V","Capacitor_THT:CP_Radial_D10.0mm_P5.00mm",""
1,"C8","100n","Capacitor_SMD:C_0805_2012Metric","C49678"
2,"C9 C5","10u 25V","Capacitor_SMD:C_0805_2012Metric","C15850"
5,"D4 D20 D21 D22 D23","B5819W","Diode_SMD:D_SOD-123","C8598"
1,"D9","SS34","Diode_SMD:D_SMA","C8678"
1,"J1","2x8 female 8.5 mm","Connector_PinHeader_2.54mm:PinHeader_2x08_P2.54mm_Vertical",""
1,"J30","PWM out, right angle","rc_crane:PinHeader_3x16_P2.54mm_Horizontal",""
1,"J4","RC in, right angle","rc_crane:PinHeader_3x04_P2.54mm_Horizontal",""
1,"J7","Serial RX, right angle","rc_crane:PinHeader_1x04_P2.54mm_Horizontal",""
1,"J8","I2C, right angle","rc_crane:PinHeader_1x04_P2.54mm_Horizontal",""
1,"J9","VM batt, side entry","Connector_JST:JST_XH_S2B-XH-A_1x02_P2.50mm_Horizontal",""
1,"JP9","VM BEC|BATT","Jumper:SolderJumper-3_P1.3mm_Open_RoundedPad1.0x1.5mm",""
1,"R11","10k","Resistor_SMD:R_0805_2012Metric","C17414"
16,"R40 R41 R42 R43 R44 R45 R46 R47 R48 R49 R50 R51 R52 R53 R54 R55","220","Resistor_SMD:R_0805_2012Metric","C17557"
6,"R7 R8 R20 R21 R22 R23","1k","Resistor_SMD:R_0805_2012Metric","C17513"
2,"R9 R10","4.7k","Resistor_SMD:R_0805_2012Metric","C17673"
1,"U4","AMS1117-5.0","Package_TO_SOT_SMD:SOT-223-3_TabPin2","C6187"
1,"U5","PCA9685PW","Package_SO:TSSOP-28_4.4x9.7mm_P0.65mm","C2678753"

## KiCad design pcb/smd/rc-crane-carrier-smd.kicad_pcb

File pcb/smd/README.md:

# SMD carrier board – ordering at JLCPCB

JLCPCB assembles all SMD parts on the top side. You solder the through‑hole parts yourself
afterwards:

| Hand soldered (not in the assembly files) | |
|---|---|
| J10, J11 | Female header 1×8 – SuperMini socket |
| U2, U3 | 4 × female header 1×8 – TMC2209 sockets |
| J12, J13 | Female header 1×1 – DIAG |
| J2, J3 | JST‑XH 4‑pin B4B‑XH‑A – motors |
| J4, J5 | Pin header 1×3 – RC channels |
| C1, C2 | 100 µF 35 V electrolytic, D8 mm, 3.5 mm pitch – driver VM buffer, **required**. Mind the `+` mark. THT because the SMD version is a JLCPCB extended part |
| JP1, JP2 | Solder jumpers – bridge with a blob of solder, see [UART pin](../README.md#before-you-order-check-these-both-variants) |

## Files

| File | Upload as |
|------|-----------|
| [`fab/rc-crane-carrier-smd-gerbers.zip`](fab/rc-crane-carrier-smd-gerbers.zip) | Gerber file |
| [`jlcpcb_bom.csv`](jlcpcb_bom.csv) | BOM (columns: Comment, Designator, Footprint, LCSC Part #) |
| [`jlcpcb_cpl.csv`](jlcpcb_cpl.csv) | CPL / pick‑and‑place (Designator, Mid X, Mid Y, Layer, Rotation) |

## Ordering steps

1. On jlcpcb.com, upload the Gerber zip. 2 layers, 1.6 mm, HASL lead‑free is fine.
2. Enable **PCB Assembly** with these settings:
   - side: top
   - type: "Economic" works, since all parts are on one side
   - "Confirm Parts Placement": on
3. Upload `jlcpcb_bom.csv` and `jlcpcb_cpl.csv`. All 12 SMD parts should match an LCSC part
   automatically. They are all JLCPCB basic parts, so there are no extended‑part fees.
   Check that none show as out of stock.
4. **Check the placement preview carefully.** KiCad and JLCPCB don't always agree on the
   zero rotation of a footprint, so polarised parts can show up rotated 180° in the
   preview. Check these against the silkscreen:

   | Ref | Polarity mark |
   |---|---|
   | D2–D6 | cathode band (the `K` side / pad 1) |
   | U4 | tab = OUT, the three pins on the left |

   You can rotate parts in the preview. With "Confirm Parts Placement" on, a JLCPCB
   engineer also checks them before production.
5. Order.

## After delivery

1. Solder C1/C2 (`+` to the marked pad), then the female headers, the JST connectors and
   the RC headers.
2. Bridge **JP1/JP2** to the UART pin of your driver brand.
3. **Before plugging in any modules:** connect the BEC to an RC header. Check about 4.6–5 V
   at the SuperMini's 5V socket pin and about 0 V at its 3V3 pin (the 3V3 rail comes from
   the SuperMini itself). Also check the BEC voltage (6 or 7.4 V) at the drivers' VM pins
   (top right pin of each driver socket).
4. Plug in the SuperMini and the drivers. **Never plug or unplug a driver or motor while
   powered.**

The parts list with LCSC links, and the reasons for the AMS1117, are in the
[PCB README](../README.md#smd-variant).

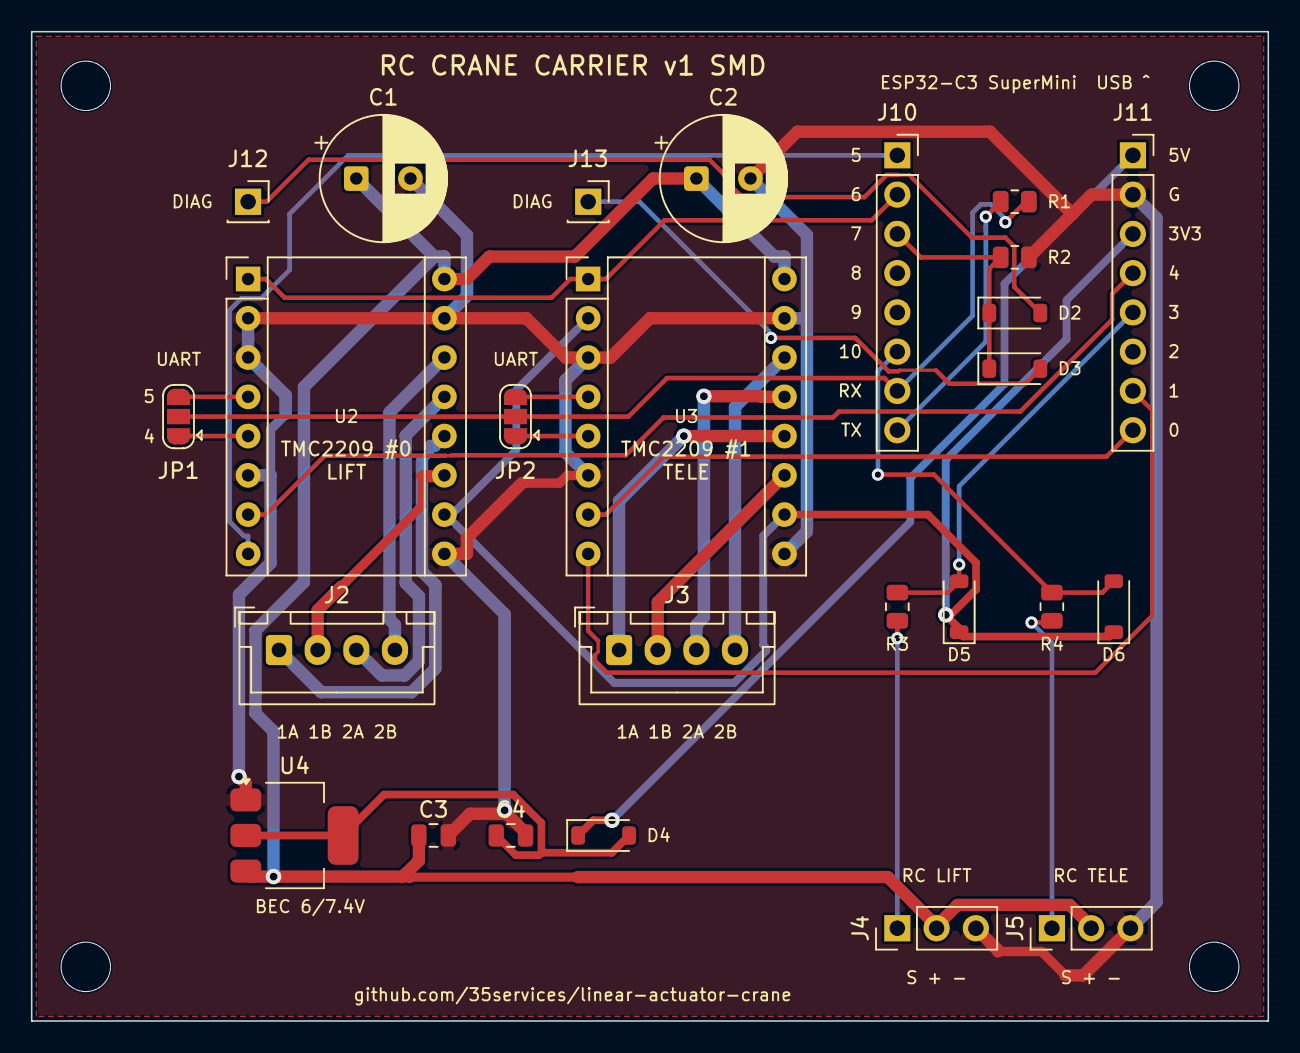
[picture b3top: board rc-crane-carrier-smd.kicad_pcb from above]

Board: 2 copper layers, 80.0 x 64.0 mm, 30 parts (0 on the bottom side), 31 nets.

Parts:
C1, C2: 100u 35V; CP_Radial_D8.0mm_P3.50mm
C3: 10u 25V; C_0805_2012Metric
C4: 22u 25V; C_0805_2012Metric
D2, D3: 1N4148W; D_SOD-123
D4, D5, D6: B5819W; D_SOD-123
H1, H2, H3, H4: MountingHole_3.2mm_M3
J2: Motor lift; JST_XH_B4B-XH-A_1x04_P2.50mm_Vertical
J3: Motor tele; JST_XH_B4B-XH-A_1x04_P2.50mm_Vertical
J4: RC lift; PinHeader_1x03_P2.54mm_Vertical
J5: RC tele; PinHeader_1x03_P2.54mm_Vertical
J10: SuperMini L; PinSocket_1x08_P2.54mm_Vertical
J11: SuperMini R; PinSocket_1x08_P2.54mm_Vertical
J12: DIAG0; PinSocket_1x01_P2.54mm_Vertical
J13: DIAG1; PinSocket_1x01_P2.54mm_Vertical
JP1, JP2: UART 4|5; SolderJumper-3_P1.3mm_Open_RoundedPad1.0x1.5mm
R1, R3, R4: 1k; R_0805_2012Metric
R2: 10k; R_0805_2012Metric
U2: TMC2209 #0 lift; Pololu_Breakout-16_15.2x20.3mm
U3: TMC2209 #1 tele; Pololu_Breakout-16_15.2x20.3mm
U4: AMS1117-5.0; SOT-223-3_TabPin2

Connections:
+3V3: D5.1, D6.1, J11.3, U2.10, U3.2, U3.10
+5V: D4.1, J11.1
+5V_REG: C4.1, D4.2, U4.2
DIAG: D2.1, D3.1, J10.3, R2.1
DIAG0: D2.2, J12.1
DIAG1: D3.2, J13.1
DIR0: J10.1, U2.8
DIR1: J11.7, U3.8
EN: J10.2, U2.1, U3.1
GND: C1.2, C2.2, C3.2, C4.2, J4.3, J5.3, J11.2, R2.2, U2.2, U2.3, U2.6, U2.9, U2.15, U3.3, U3.6, U3.9, U3.15, U4.1
M0_1A: J2.1, U2.12
M0_1B: J2.2, U2.11
M0_2A: J2.3, U2.13
M0_2B: J2.4, U2.14
M1_1A: J3.1, U3.12
M1_1B: J3.2, U3.11
M1_2A: J3.3, U3.13
M1_2B: J3.4, U3.14
RC0: D5.2, J11.5, R3.2
RC0_IN: J4.1, R3.1
RC1: D6.2, J10.6, R4.2
RC1_IN: J5.1, R4.1
STEP0: J11.4, U2.7
STEP1: J11.8, U3.7
U0_P4: JP1.3, U2.4
U0_P5: JP1.1, U2.5
U1_P4: JP2.3, U3.4
U1_P5: JP2.1, U3.5
UART: J10.7, JP1.2, JP2.2, R1.2
UART_TX: J10.8, R1.1
VBEC: C1.1, C2.1, C3.1, J4.2, J5.2, U2.16, U3.16, U4.3

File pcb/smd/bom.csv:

Qty,References,Value,Footprint,LCSC
2,"C1 C2","100u 35V","Capacitor_THT:CP_Radial_D8.0mm_P3.50mm",""
1,"C3","10u 25V","Capacitor_SMD:C_0805_2012Metric","C15850"
1,"C4","22u 25V","Capacitor_SMD:C_0805_2012Metric","C45783"
2,"D2 D3","1N4148W","Diode_SMD:D_SOD-123","C81598"
3,"D4 D5 D6","B5819W","Diode_SMD:D_SOD-123","C8598"
1,"J10","SuperMini L","Connector_PinSocket_2.54mm:PinSocket_1x08_P2.54mm_Vertical",""
1,"J11","SuperMini R","Connector_PinSocket_2.54mm:PinSocket_1x08_P2.54mm_Vertical",""
1,"J12","DIAG0","Connector_PinSocket_2.54mm:PinSocket_1x01_P2.54mm_Vertical",""
1,"J13","DIAG1","Connector_PinSocket_2.54mm:PinSocket_1x01_P2.54mm_Vertical",""
1,"J2","Motor lift","Connector_JST:JST_XH_B4B-XH-A_1x04_P2.50mm_Vertical",""
1,"J3","Motor tele","Connector_JST:JST_XH_B4B-XH-A_1x04_P2.50mm_Vertical",""
1,"J4","RC lift","Connector_PinHeader_2.54mm:PinHeader_1x03_P2.54mm_Vertical",""
1,"J5","RC tele","Connector_PinHeader_2.54mm:PinHeader_1x03_P2.54mm_Vertical",""
2,"JP1 JP2","UART 4|5","Jumper:SolderJumper-3_P1.3mm_Open_RoundedPad1.0x1.5mm",""
3,"R1 R3 R4","1k","Resistor_SMD:R_0805_2012Metric","C17513"
1,"R2","10k","Resistor_SMD:R_0805_2012Metric","C17414"
1,"U2","TMC2209 #0 lift","Module:Pololu_Breakout-16_15.2x20.3mm",""
1,"U3","TMC2209 #1 tele","Module:Pololu_Breakout-16_15.2x20.3mm",""
1,"U4","AMS1117-5.0","Package_TO_SOT_SMD:SOT-223-3_TabPin2","C6187"
